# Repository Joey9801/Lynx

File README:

Lynx is an experimental radio transmitter for HAB's

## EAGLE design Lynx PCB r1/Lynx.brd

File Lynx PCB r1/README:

eagle project

components not in the default libraries are in ../Lynx\ components.lbr

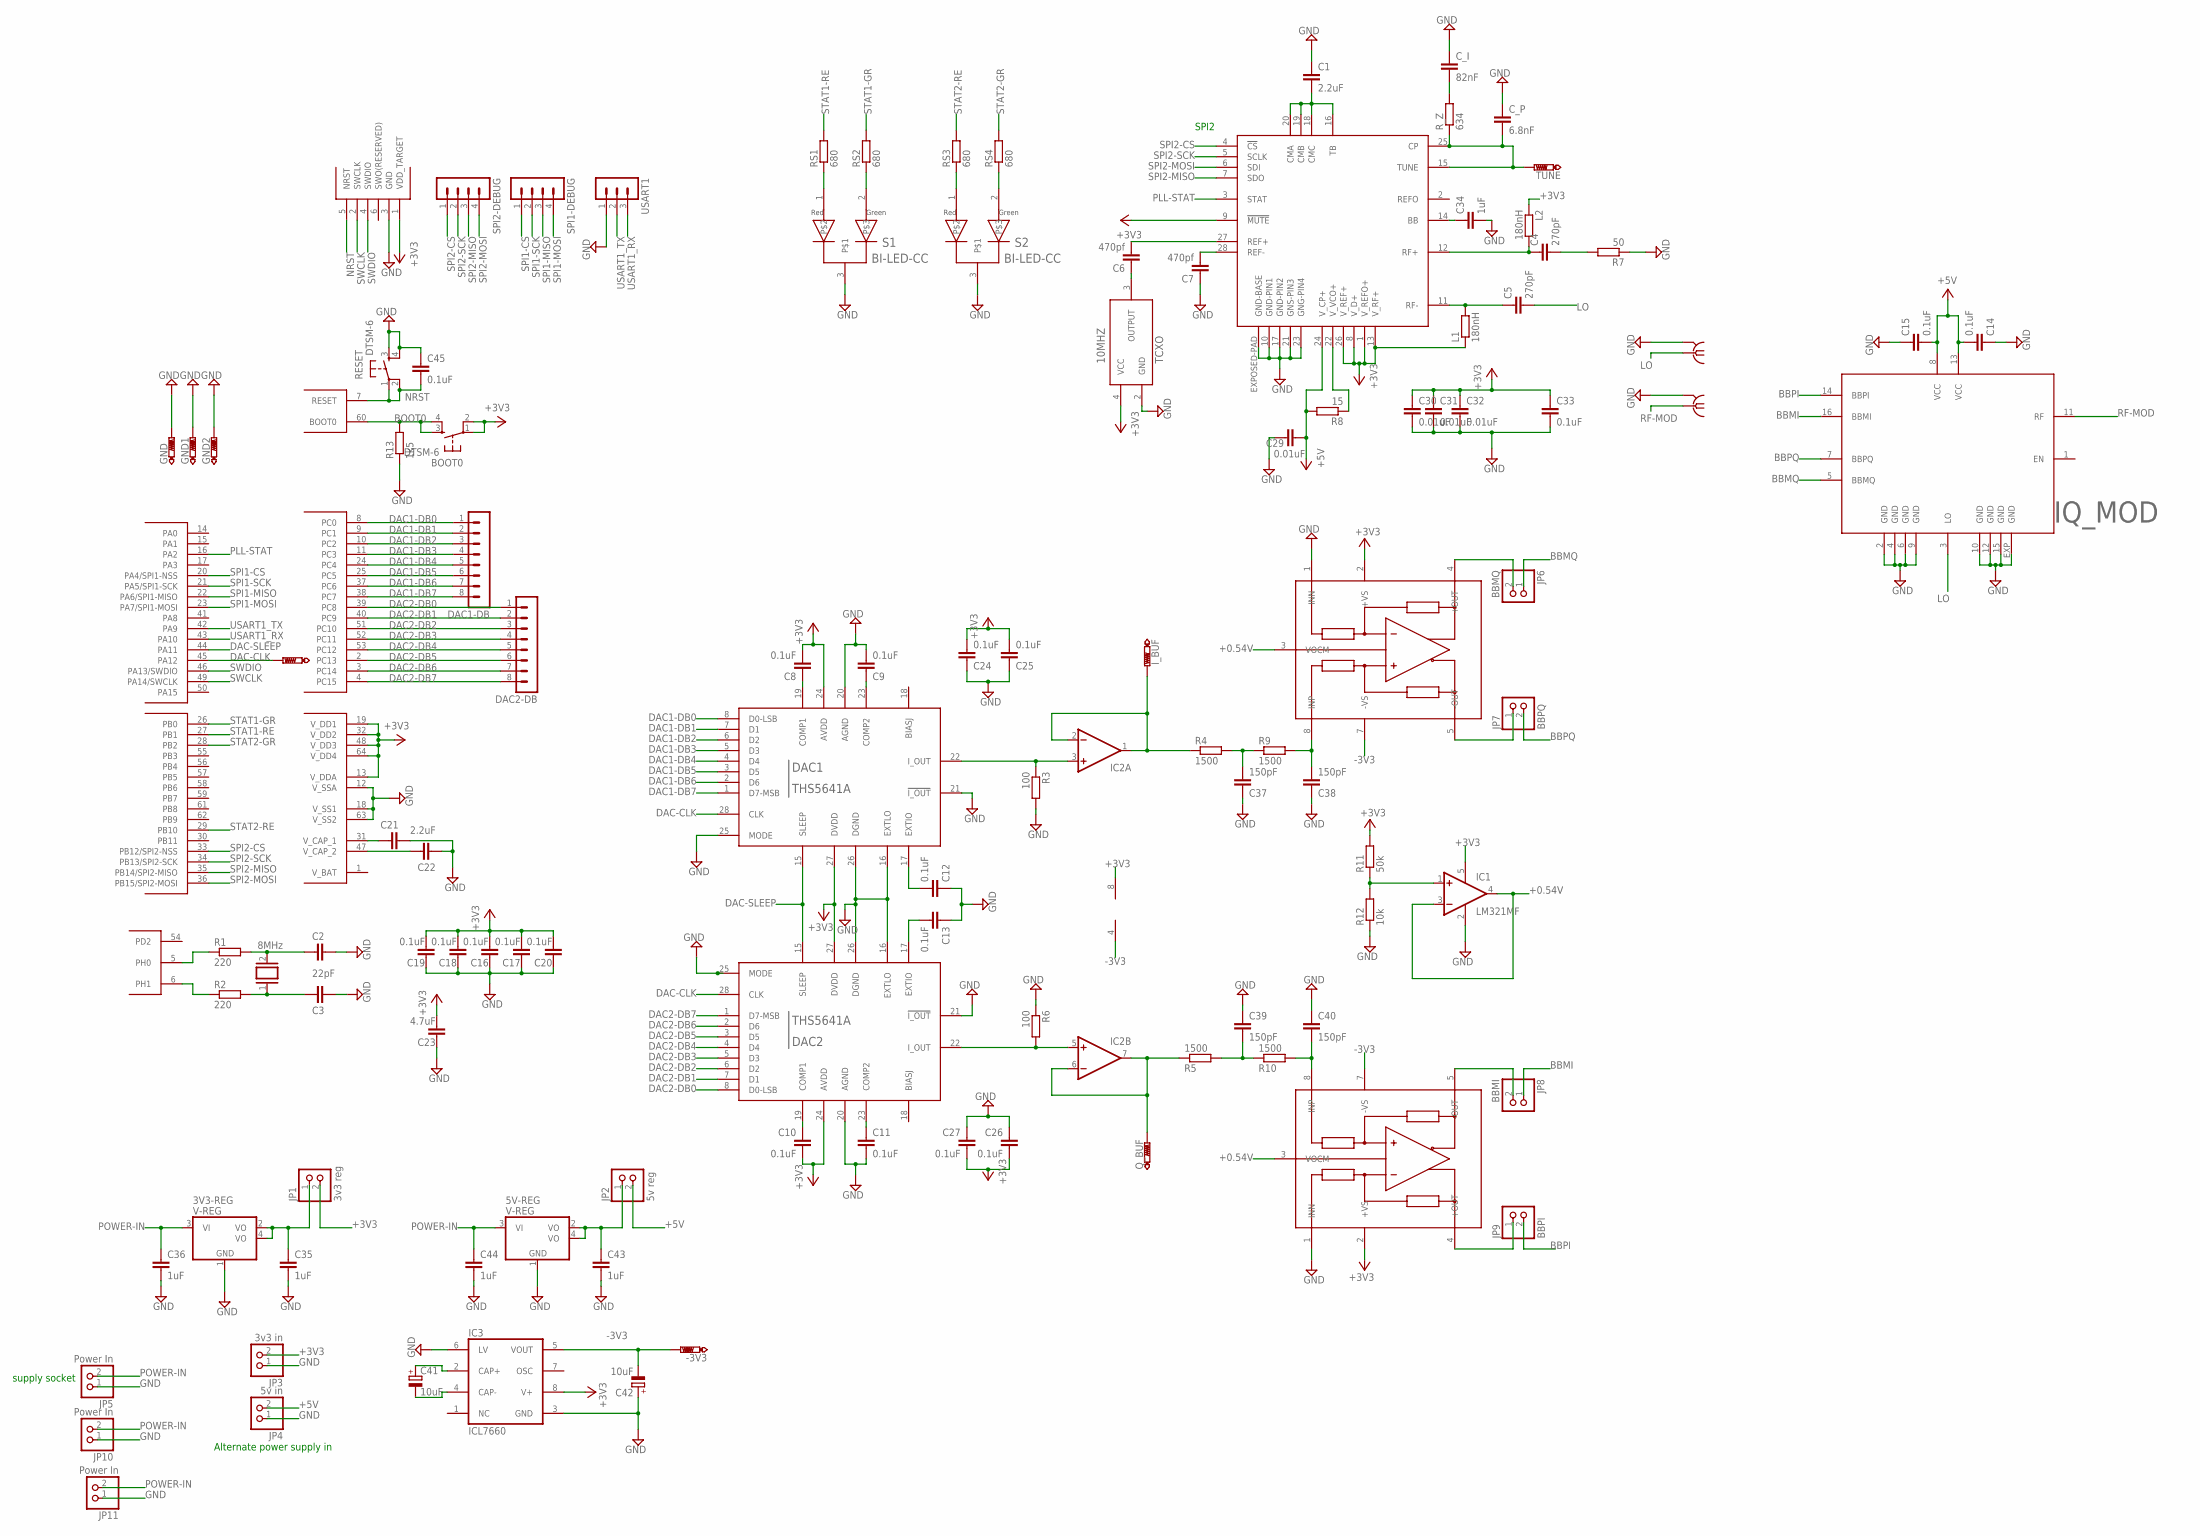
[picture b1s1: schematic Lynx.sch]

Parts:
3V3-REG, 5V-REG: V-REG; SOT223
10MHZ: TCXO; TXCO5.6
-3V3: PTR1PAD1-13Y; P1-13Y
BOOT0: DTSM-6
C1, C21, C22: 2.2uF; C0603
C2, C3: 22pF; C0603
C4, C5: 270pF; C0805
C6, C7: 470pf; C0402
C8, C9, C10, C11, C12, C13, C14, C15, C16, C17, C18, C19, C20, C24, C25, C26, C27, C33, C45: 0.1uF; C0603
C23: 4.7uF; C0603
C29, C30, C32: 0.01uF; C0603
C31: 0.01uF; C0402
C34, C35, C36, C43, C44: 1uF; C0603
C37, C38, C39, C40: 150pF; C0603
C41, C42: 10uF; SANYO-OSCON_SMD_B6
C_I: 82nF; C1210
C_P: 6.8nF; C0805
DAC1, DAC2: THS5641A; SO28
DAC1-DB, DAC2-DB: MA08-1
DAC-CLK: PTR1PAD1-13Y; P1-13Y
GND, GND1, GND2: PTR1PAD1-13Y; P1-13Y
IC1: LM321MF; SOT23-5
IC2: 2AMP_P8+4D; SO08
IC3: ICL7660; SO08
IQ_MOD: LT5568; QFN-16
I_BUF: PTR1PAD1-13Y; P1-13Y
JP1: 3v3 reg; 1X02
JP2: 5v reg; 1X02
JP3: 3v3 in; 1X02
JP4: 5v in; 1X02
JP5, JP10, JP11: Power In; 1X02
JP6: BBMQ; 1X02
JP7: BBPQ; 1X02
JP8: BBMI; 1X02
JP9: BBPI; 1X02
L1, L2: 180nH; R0402
LO: SMA-142-0711-821/826; J502-ND-142-0711-821/826
Q1: 8MHz; QS
Q_BUF: PTR1PAD1-13Y; P1-13Y
R1, R2: 220; R0603
R3, R6: 100; R0603
R4, R5, R9, R10: 1500; R0603
R7: 50; R0805
R8: 15; R0603
R11: 50k; R0603
R12: 10k; R0603
R13: 1k5; R0603
RESET: DTSM-6
RF-MOD: SMA-142-0711-821/826; J502-ND-142-0711-821/826
RS1, RS2, RS3, RS4: 680; R0603
R_Z: 634; R0805
S1, S2: BI-LED-CC; SOT-23
SPI1-DEBUG, SPI2-DEBUG: MA04-1
SWD-HEADER: SWD-HEADER; 6PIN-HEADER
TUNE: PTR1B1,27; B1,27
U$1: STM32F415RGT6; LQFP-64
U$3: LTC6946; QFN-28
U$4, U$5: AD8476; MSOP8
USART1: MA03-1

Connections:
5V-REG: 5V-REG.2 (VO), 5V-REG.4 (VO), C43.1, JP2.1
+0.54V: IC1.3 (-IN), IC1.4 (OUT), U$4.3 (VOCM), U$5.3 (VOCM)
+3V3: 10MHZ.4 (VCC), BOOT0.1, BOOT0.2, C8.2, C10.2, C16.2, C17.2, C18.2, C19.2, C20.2, C23.2, C24.2, C25.2, C26.2, C27.2, C30.1, C31.1, C32.1, C33.1, DAC1.24 (AVDD), DAC1.27 (DVDD), DAC2.24 (AVDD), DAC2.27 (DVDD), IC1.5 (V+), IC2.8 (V+), IC3.8 (V+), JP1.2, JP3.2, L1.1, L2.1, R11.2, SWD-HEADER.1 (VDD_TARGET), U$1.13 (V_DDA), U$1.19 (V_DD1), U$1.32 (V_DD2), U$1.48 (V_DD3), U$1.64 (V_DD4), U$3.1 (V_REFO+), U$3.8 (V_D+), U$3.9 (!MUTE!), U$3.13 (V_RF+), U$3.26 (V_REF+), U$4.2 (+VS), U$5.2 (+VS)
+5V: C14.2, C15.2, C29.2, IQ_MOD.8 (VCC), IQ_MOD.13 (VCC), JP2.2, JP4.2, R8.2, U$3.24 (V_CP+)
-3V3: -3V3.TP, C42.-, IC2.4 (V-), IC3.5 (VOUT), U$4.7 (-VS), U$5.7 (-VS)
BBMI: IQ_MOD.16 (BBMI), JP8.1
BBMQ: IQ_MOD.5 (BBMQ), JP6.1
BBPI: IQ_MOD.14 (BBPI), JP9.2
BBPQ: IQ_MOD.7 (BBPQ), JP7.2
BOOT0: BOOT0.3, BOOT0.4, R13.2, U$1.60 (BOOT0)
DAC1-DB0: DAC1.8 (D0-LSB), DAC1-DB.1, U$1.8 (PC0)
DAC1-DB1: DAC1.7 (D1), DAC1-DB.2, U$1.9 (PC1)
DAC1-DB2: DAC1.6 (D2), DAC1-DB.3, U$1.10 (PC2)
DAC1-DB3: DAC1.5 (D3), DAC1-DB.4, U$1.11 (PC3)
DAC1-DB4: DAC1.4 (D4), DAC1-DB.5, U$1.24 (PC4)
DAC1-DB5: DAC1.3 (D5), DAC1-DB.6, U$1.25 (PC5)
DAC1-DB6: DAC1.2 (D6), DAC1-DB.7, U$1.37 (PC6)
DAC1-DB7: DAC1.1 (D7-MSB), DAC1-DB.8, U$1.38 (PC7)
DAC2-DB0: DAC2.8 (D0-LSB), DAC2-DB.1, U$1.39 (PC8)
DAC2-DB1: DAC2.7 (D1), DAC2-DB.2, U$1.40 (PC9)
DAC2-DB2: DAC2.6 (D2), DAC2-DB.3, U$1.51 (PC10)
DAC2-DB3: DAC2.5 (D3), DAC2-DB.4, U$1.52 (PC11)
DAC2-DB4: DAC2.4 (D4), DAC2-DB.5, U$1.53 (PC12)
DAC2-DB5: DAC2.3 (D5), DAC2-DB.6, U$1.2 (PC13)
DAC2-DB6: DAC2.2 (D6), DAC2-DB.7, U$1.3 (PC14)
DAC2-DB7: DAC2.1 (D7-MSB), DAC2-DB.8, U$1.4 (PC15)
DAC-CLK: DAC1.28 (CLK), DAC2.28 (CLK), DAC-CLK.TP, U$1.45 (PA12)
DAC-SLEEP: DAC1.15 (SLEEP), DAC2.15 (SLEEP), U$1.44 (PA11)
GND: 3V3-REG.1 (GND), 5V-REG.1 (GND), 10MHZ.2 (GND), C1.1, C2.2, C3.2, C7.1, C9.2, C11.2, C12.1, C13.1, C14.1, C15.1, C16.1, C17.1, C18.1, C19.1, C20.1, C21.2, C22.2, C23.1, C24.1, C25.1, C26.1, C27.1, C29.1, C30.2, C31.2, C32.2, C33.2, C34.2, C35.2, C36.2, C37.1, C38.1, C39.1, C40.1, C42.+, C43.2, C44.2, C45.1, C_I.1, C_P.1, DAC1.16 (EXTLO), DAC1.20 (AGND), DAC1.21 (!I_OUT!), DAC1.25 (MODE), DAC1.26 (DGND), DAC2.16 (EXTLO), DAC2.20 (AGND), DAC2.21 (!I_OUT!), DAC2.25 (MODE), DAC2.26 (DGND), GND.TP, GND1.TP, GND2.TP, IC1.2 (V-), IC3.3 (GND), IC3.6 (LV), IQ_MOD.2 (GND), IQ_MOD.4 (GND), IQ_MOD.6 (GND), IQ_MOD.9 (GND), IQ_MOD.10 (GND), IQ_MOD.12 (GND), IQ_MOD.15 (GND), IQ_MOD.EXP (GND), JP3.1, JP4.1, JP5.1, JP10.1, JP11.1, LO.G@1 (2), LO.G@2 (2), LO.G@3 (2), LO.G@4 (2), R3.2, R6.1, R7.1, R12.1, R13.1, RESET.3, RESET.4, RF-MOD.G@1 (2), RF-MOD.G@2 (2), RF-MOD.G@3 (2), RF-MOD.G@4 (2), S1.3, S2.3, SWD-HEADER.3 (GND), U$1.12 (V_SSA), U$1.18 (V_SS1), U$1.63 (V_SS2), U$3.10 (GND-PIN1), U$3.17 (GND-PIN2), U$3.21 (GNS-PIN3), U$3.23 (GNG-PIN4), U$3.EXPOSED-PAD (GND-BASE), U$4.1 (INN), U$5.1 (INN), USART1.1
I_BUF: IC2.1 (OUT), IC2.2 (-IN), I_BUF.TP, R4.1
LO: C5.2, IQ_MOD.3 (LO), LO.1
unnamed: C_P.2, R_Z.1, TUNE.TP, U$3.15 (TUNE), U$3.25 (CP)
unnamed: C1.2, U$3.16 (TB), U$3.18 (CMC), U$3.19 (CMB), U$3.20 (CMA)
unnamed: C7.2, U$3.28 (REF-)
unnamed: C3.1, Q1.1, R2.2
unnamed: C2.1, Q1.2, R1.2
unnamed: R1.1, U$1.5 (PH0)
unnamed: R2.1, U$1.6 (PH1)
unnamed: C5.1, L1.2, U$3.11 (RF-)
unnamed: C4.2, R7.2
unnamed: C13.2, DAC2.17 (EXTIO)
unnamed: C8.1, DAC1.19 (COMP1)
unnamed: C12.2, DAC1.17 (EXTIO)
unnamed: DAC1.22 (I_OUT), IC2.3 (+IN), R3.1
unnamed: JP6.2, U$4.4 (+OUT)
unnamed: RS1.1, S1.1
unnamed: RS2.1, S1.2
unnamed: RS3.1, S2.1
unnamed: RS4.1, S2.2
unnamed: C10.1, DAC2.19 (COMP1)
unnamed: C6.2, U$3.27 (REF+)
unnamed: 10MHZ.3 (OUTPUT), C6.1
unnamed: C_I.2, R_Z.2
unnamed: C9.1, DAC1.23 (COMP2)
unnamed: C11.1, DAC2.23 (COMP2)
unnamed: C21.1, U$1.31 (V_CAP_1)
unnamed: C22.1, U$1.47 (V_CAP_2)
unnamed: JP7.1, U$4.5 (-OUT)
unnamed: DAC2.22 (I_OUT), IC2.5 (+IN), R6.2
unnamed: R8.1, U$3.22 (V_VCO+)
unnamed: C37.2, R4.2, R9.1
unnamed: C38.2, R9.2, U$4.8 (INP)
unnamed: C34.1, U$3.14 (BB)
unnamed: C41.-, IC3.4 (CAP-)
unnamed: C39.2, R5.2, R10.1
unnamed: C40.2, R10.2, U$5.8 (INP)
unnamed: C41.+, IC3.2 (CAP+)
unnamed: 3V3-REG.2 (VO), 3V3-REG.4 (VO), C35.1, JP1.1
unnamed: JP8.2, U$5.5 (-OUT)
unnamed: JP9.1, U$5.4 (+OUT)
unnamed: IC1.1 (+IN), R11.1, R12.2
NRST: C45.2, RESET.1, RESET.2, SWD-HEADER.5 (NRST), U$1.7 (RESET)
PLL-STAT: U$1.16 (PA2), U$3.3 (STAT)
POWER-IN: 3V3-REG.3 (VI), 5V-REG.3 (VI), C36.1, C44.1, JP5.2, JP10.2, JP11.2
Q_BUF: IC2.6 (-IN), IC2.7 (OUT), Q_BUF.TP, R5.1
RF+: C4.1, L2.2, U$3.12 (RF+)
RF-MOD: IQ_MOD.11 (RF), RF-MOD.1
SPI1-CS: SPI1-DEBUG.1, U$1.20 (PA4/SPI1-NSS)
SPI1-MISO: SPI1-DEBUG.3, U$1.22 (PA6/SPI1-MISO)
SPI1-MOSI: SPI1-DEBUG.4, U$1.23 (PA7/SPI1-MOSI)
SPI1-SCK: SPI1-DEBUG.2, U$1.21 (PA5/SPI1-SCK)
SPI2-CS: SPI2-DEBUG.1, U$1.33 (PB12/SPI2-NSS), U$3.4 (!CS!)
SPI2-MISO: SPI2-DEBUG.3, U$1.35 (PB14/SPI2-MISO), U$3.7 (SDO)
SPI2-MOSI: SPI2-DEBUG.4, U$1.36 (PB15/SPI2-MOSI), U$3.6 (SDI)
SPI2-SCK: SPI2-DEBUG.2, U$1.34 (PB13/SPI2-SCK), U$3.5 (SCLK)
STAT1-GR: RS2.2, U$1.26 (PB0)
STAT1-RE: RS1.2, U$1.27 (PB1)
STAT2-GR: RS4.2, U$1.28 (PB2)
STAT2-RE: RS3.2, U$1.29 (PB10)
SWCLK: SWD-HEADER.2 (SWCLK), U$1.49 (PA14/SWCLK)
SWDIO: SWD-HEADER.4 (SWDIO), U$1.46 (PA13/SWDIO)
USART1_RX: U$1.43 (PA10), USART1.3
USART1_TX: U$1.42 (PA9), USART1.2

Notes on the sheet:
Alternate power supply in
supply socket
SPI2

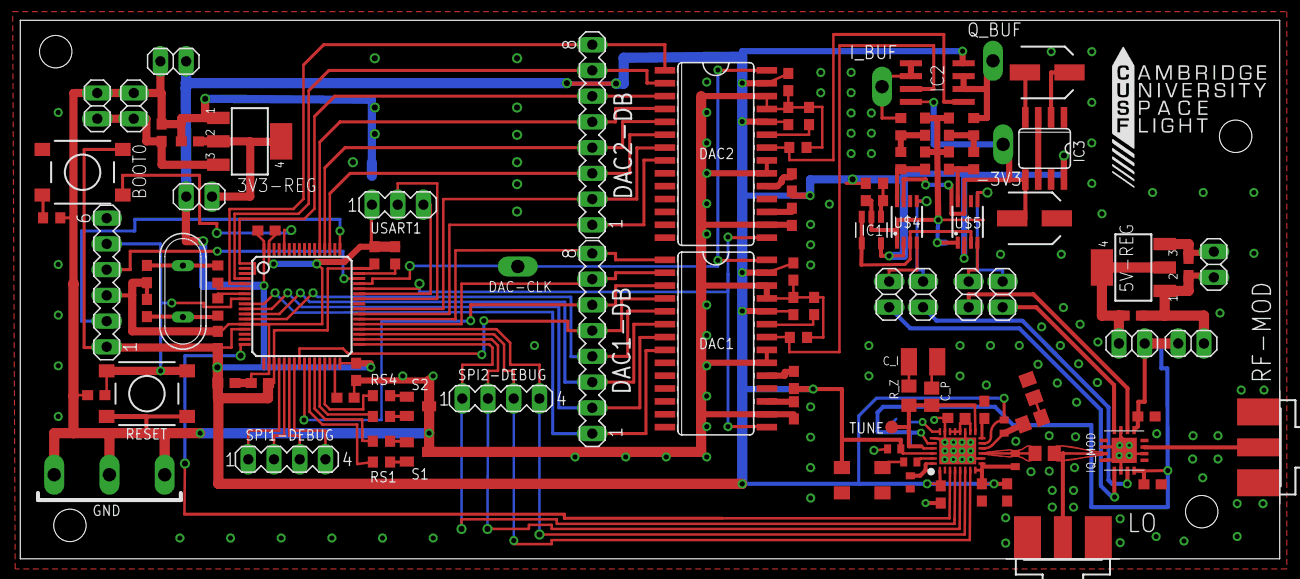
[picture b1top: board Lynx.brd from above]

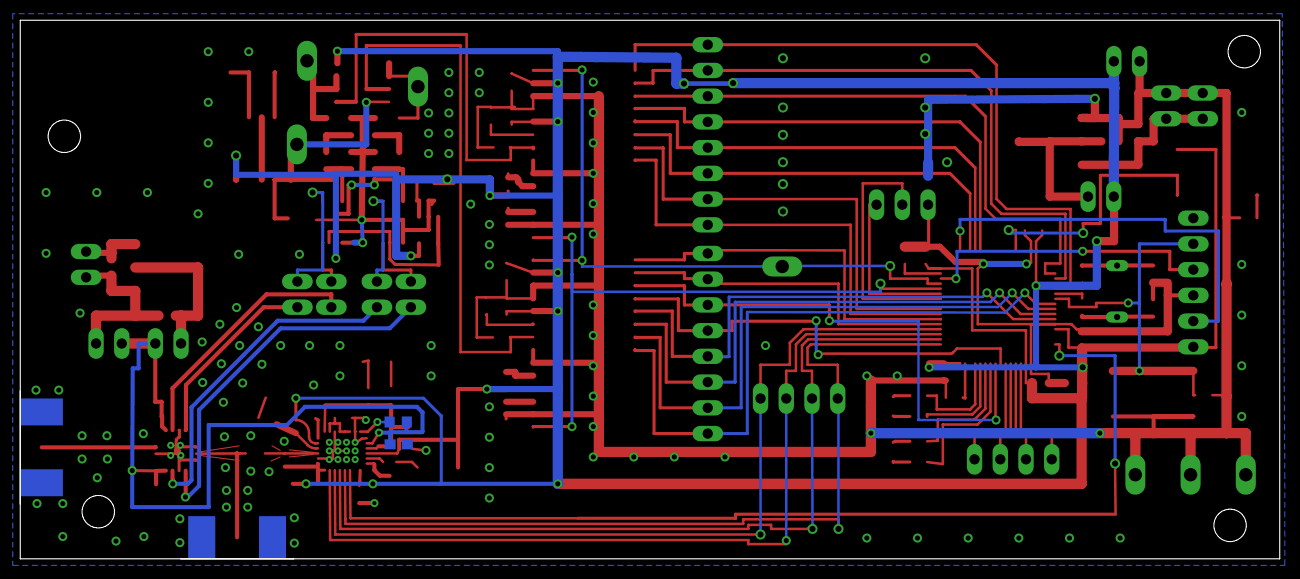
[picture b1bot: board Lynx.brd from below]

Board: 2 copper layers, 124.3 x 53.1 mm, 112 parts (2 on the bottom side), 93 nets.

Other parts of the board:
U$2: CUSF_LOGO

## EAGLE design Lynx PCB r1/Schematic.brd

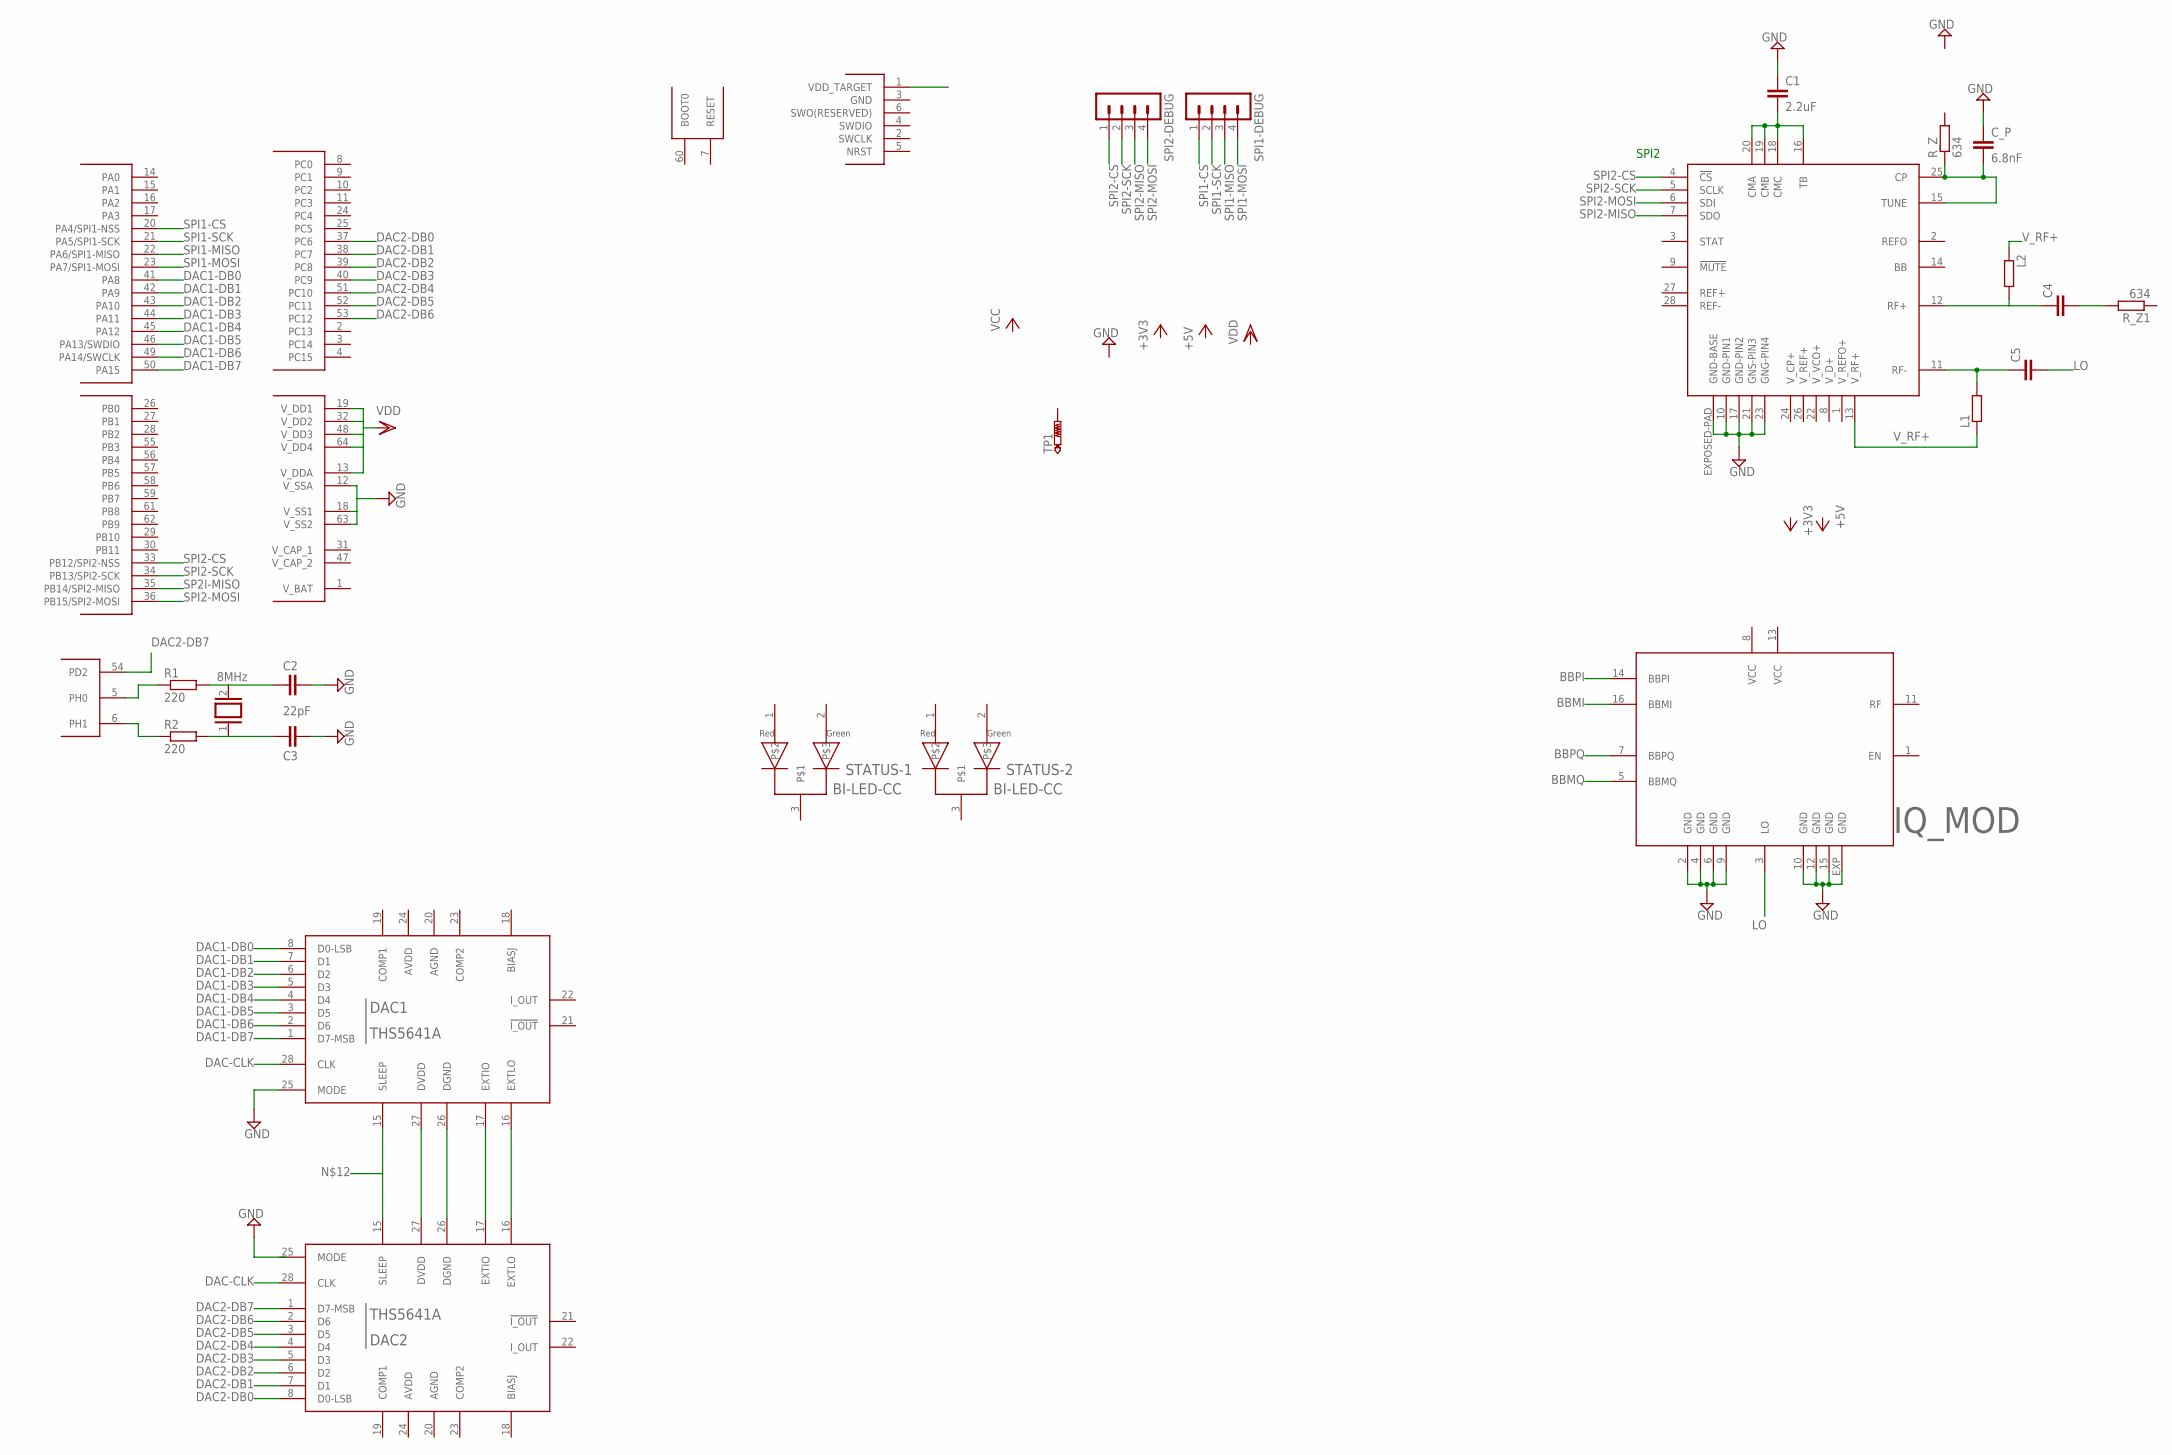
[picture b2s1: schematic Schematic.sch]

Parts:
C1: 2.2uF; C0603
C2, C3: 22pF; C0603
C4, C5: C-EUC1210; C1210
C_P: 6.8nF; C0805
DAC1, DAC2: THS5641A; SO28
IQ_MOD: LT5568; QFN-16
L1, L2: R-EU_R0402; R0402
Q1: 8MHz; QS
R1, R2: 220; R0603
R_Z, R_Z1: 634; R0805
SPI1-DEBUG, SPI2-DEBUG: MA04-1
STATUS-1, STATUS-2: BI-LED-CC; SOT-23
TP1: PTR1PAD1-20Y; P1-20Y
U$1: STM32F415RGT6; LQFP-64
U$2: SWD-HEADER; 6PIN-HEADER
U$3: LTC6946; QFN-28

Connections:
BBMI: IQ_MOD.16 (BBMI)
BBMQ: IQ_MOD.5 (BBMQ)
BBPI: IQ_MOD.14 (BBPI)
BBPQ: IQ_MOD.7 (BBPQ)
DAC1-DB0: DAC1.8 (D0-LSB), U$1.41 (PA8)
DAC1-DB1: DAC1.7 (D1), U$1.42 (PA9)
DAC1-DB2: DAC1.6 (D2), U$1.43 (PA10)
DAC1-DB3: DAC1.5 (D3), U$1.44 (PA11)
DAC1-DB4: DAC1.4 (D4), U$1.45 (PA12)
DAC1-DB5: DAC1.3 (D5), U$1.46 (PA13/SWDIO)
DAC1-DB6: DAC1.2 (D6), U$1.49 (PA14/SWCLK)
DAC1-DB7: DAC1.1 (D7-MSB), U$1.50 (PA15)
DAC2-DB0: DAC2.8 (D0-LSB), U$1.37 (PC6)
DAC2-DB1: DAC2.7 (D1), U$1.38 (PC7)
DAC2-DB2: DAC2.6 (D2), U$1.39 (PC8)
DAC2-DB3: DAC2.5 (D3), U$1.40 (PC9)
DAC2-DB4: DAC2.4 (D4), U$1.51 (PC10)
DAC2-DB5: DAC2.3 (D5), U$1.52 (PC11)
DAC2-DB6: DAC2.2 (D6), U$1.53 (PC12)
DAC2-DB7: DAC2.1 (D7-MSB), U$1.54 (PD2)
DAC-CLK: DAC1.28 (CLK), DAC2.28 (CLK)
GND: C1.1, C2.2, C3.2, C_P.1, DAC1.25 (MODE), IQ_MOD.2 (GND), IQ_MOD.4 (GND), IQ_MOD.6 (GND), IQ_MOD.9 (GND), IQ_MOD.10 (GND), IQ_MOD.12 (GND), IQ_MOD.15 (GND), IQ_MOD.EXP (GND), U$1.12 (V_SSA), U$1.18 (V_SS1), U$1.63 (V_SS2), U$3.10 (GND-PIN1), U$3.17 (GND-PIN2), U$3.21 (GNS-PIN3), U$3.23 (GNG-PIN4), U$3.EXPOSED-PAD (GND-BASE)
LO: C5.2, IQ_MOD.3 (LO)
unnamed: C_P.2, R_Z.1, U$3.15 (TUNE), U$3.25 (CP)
unnamed: C1.2, U$3.16 (TB), U$3.18 (CMC), U$3.19 (CMB), U$3.20 (CMA)
unnamed: C3.1, Q1.1, R2.2
unnamed: C2.1, Q1.2, R1.2
unnamed: R1.1, U$1.5 (PH0)
unnamed: R2.1, U$1.6 (PH1)
unnamed: C5.1, L1.2, U$3.11 (RF-)
unnamed: C4.1, L2.2, U$3.12 (RF+)
unnamed: C4.2, R_Z1.2
unnamed: DAC1.27 (DVDD), DAC2.27 (DVDD)
unnamed: DAC1.15 (SLEEP), DAC2.15 (SLEEP)
unnamed: DAC1.26 (DGND), DAC2.26 (DGND)
unnamed: DAC1.17 (EXTIO), DAC2.17 (EXTIO)
unnamed: DAC1.16 (EXTLO), DAC2.16 (EXTLO)
SP2I-MISO: U$1.35 (PB14/SPI2-MISO)
SPI1-CS: SPI1-DEBUG.1, U$1.20 (PA4/SPI1-NSS)
SPI1-MISO: SPI1-DEBUG.3, U$1.22 (PA6/SPI1-MISO)
SPI1-MOSI: SPI1-DEBUG.4, U$1.23 (PA7/SPI1-MOSI)
SPI1-SCK: SPI1-DEBUG.2, U$1.21 (PA5/SPI1-SCK)
SPI2-CS: SPI2-DEBUG.1, U$1.33 (PB12/SPI2-NSS), U$3.4 (!CS!)
SPI2-MISO: SPI2-DEBUG.3, U$3.7 (SDO)
SPI2-MOSI: SPI2-DEBUG.4, U$1.36 (PB15/SPI2-MOSI), U$3.6 (SDI)
SPI2-SCK: SPI2-DEBUG.2, U$1.34 (PB13/SPI2-SCK), U$3.5 (SCLK)
VDD: U$1.13 (V_DDA), U$1.19 (V_DD1), U$1.32 (V_DD2), U$1.48 (V_DD3), U$1.64 (V_DD4)
V_RF+: L1.1, L2.1, U$3.13 (V_RF+)

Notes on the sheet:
SPI2

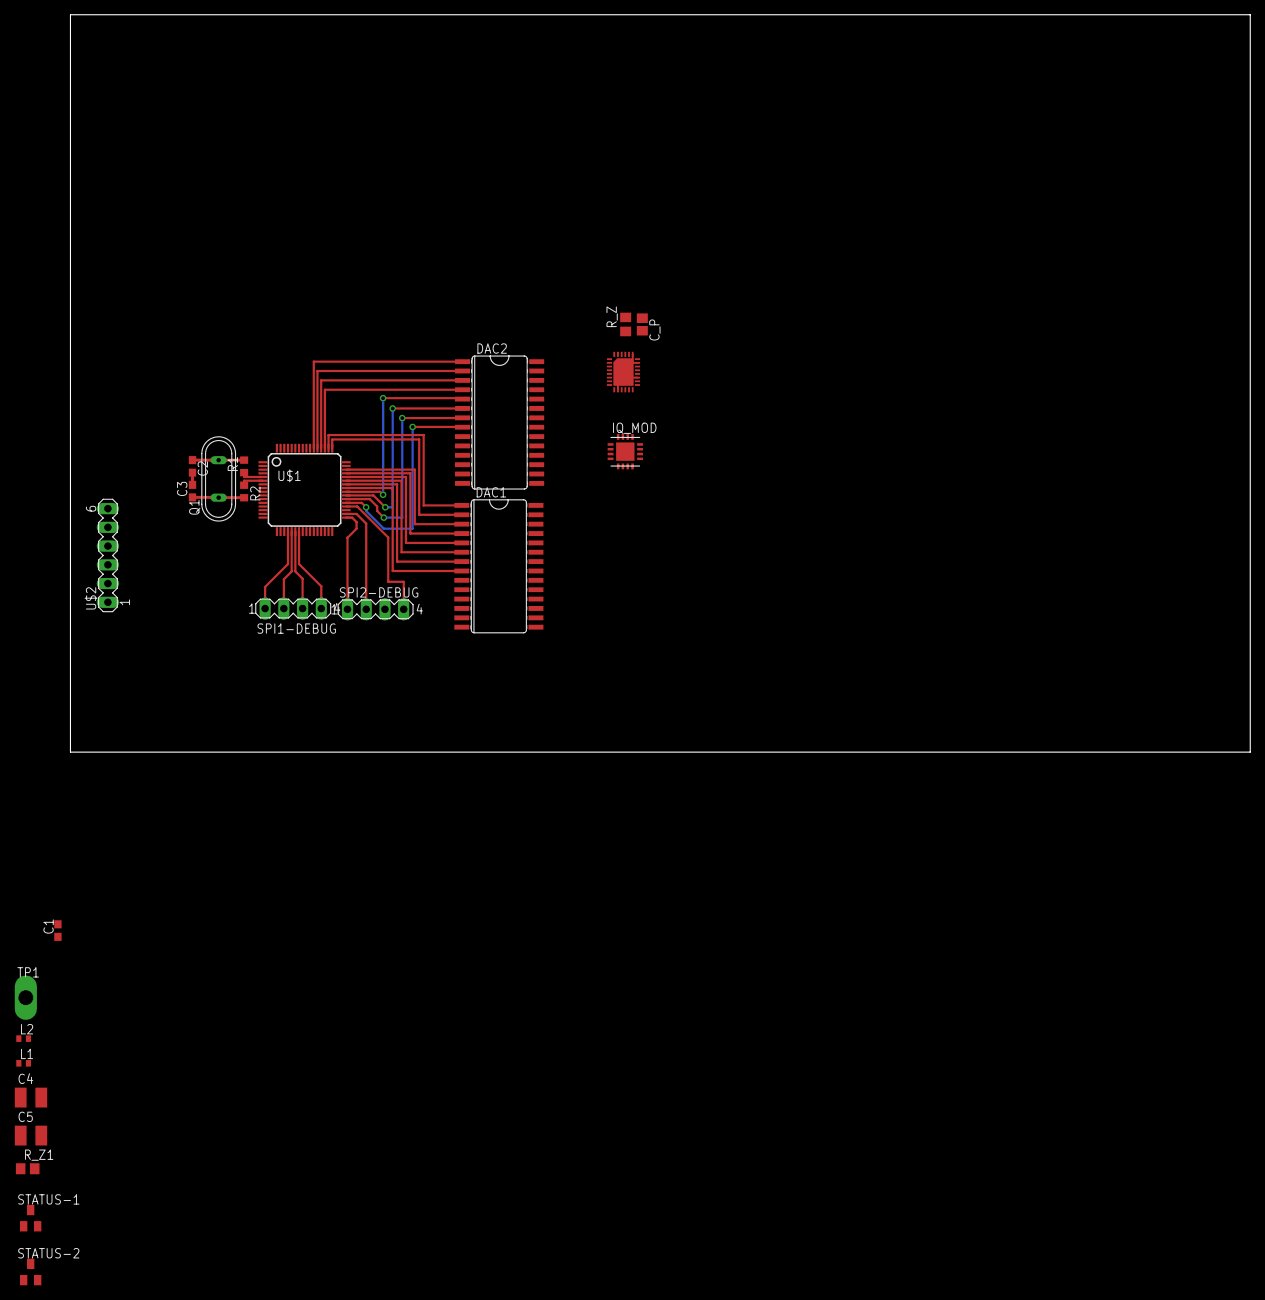
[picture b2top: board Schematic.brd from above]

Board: 2 copper layers, 160.0 x 100.0 mm, 24 parts (0 on the bottom side), 43 nets.

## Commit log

2013-06-23 Makefile and linker
2013-06-28 playground
2013-07-01 usart working
2013-07-01 readme
2013-07-01 fir WIP
2013-07-02 fir declarations
2013-07-02 init prototypes
2013-07-05 PCB r1 wip
2013-07-05 Revert "PCB r1 wip"
    This reverts commit 15770d55321f7ac96c8f35ec2526d0d9f5ee7b52.
2013-07-05 pcb commit (no fail this time)
2013-07-05 PCB WIP
2013-07-10 library
2013-07-10 rf routing
2013-07-10 made the spi work woop woop
2013-07-11 Power supply and jumpers
    So many jumpers
2013-07-11 tidy up
2013-07-11 more tidy up
2013-07-12 Complete rf reroute
    Shuffled a 'lot' of things around. Ripped up everything past the op-amps
    and made it a lot nicer.
2013-07-12 All routed
2013-07-12 Added 0.54v reference souce, made DRC happy
2013-07-12 Description text, pll-stat line
2013-07-12 started sorting out the silkscreen
2013-07-12 more silk
2013-07-14 Finished first pass of silk
    Finished organizing the first revision of the artwork. Added pin names
    to all busses. Created a dac-clk test pin
2013-07-14 Gerbers
2013-07-15 Changes as per Cillian
    Changed the layout of the RF
    swapped out the coax connectors
    added "TUNE" test point
    revamped the ground planes
    stitched the ground planes (a lot)
2013-07-16 Final PCB r1 commit
    Fixed lots of little thing.
    Gerbers checked
    Fixed 0.54v generation oopsie (inverting and non-inverting terminals
    wrong way around)
2013-07-16 What was send to the board house
2013-07-17 some init code and placeholer parity ecc
2013-07-17 all init prototypes, main loop
2013-07-17 constellation placeholders
2013-07-18 fiddled with the todo
2013-07-18 fixed silly things, now compiles
2013-07-18 timer sheduling tests
2013-07-19 lots of sheduling, timers configured
2013-07-19 fixed transmit hang in main todo loop
2013-07-19 setup TIM5 as function timer
2013-07-19 fixed function declare
2013-07-23 pll setup begin
2013-07-25 pll and dac setups
2013-07-25 started documentation
2013-07-26 more DOC
2013-07-26 fixed error in usart_setup()
2013-07-26 swapped 'status' out for set of bools
2013-07-26 Updated DOC to relfect new status
2013-08-01 virtualbox fail commit
2013-09-12 Oh shii.. haven't committed in ages
2013-09-13 skeleton code for waveform test
2013-09-18 waveform test compiles
2013-09-23 Week 8 commit
2013-09-23 src compiles - no cmath still
2013-09-25 Basic do_constellation() function writen
